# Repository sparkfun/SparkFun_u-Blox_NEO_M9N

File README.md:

SparkFun GPS NEO-M9N Breakout (Chip Antenna, U.FL, SMA) 
========================================

<table class="table table-hover table-striped table-bordered">
  <tr align="center">
   <td></td>
   <td></td>
    <td></td>
  </tr>
  <tr align="center">
    <td><a href="https://www.sparkfun.com/products/15733">SparkFun GPS NEO-M9N Chip Antenna <br />(GPS-15733)</a></td>
    <td><a href="https://www.sparkfun.com/products/15712">SparkFun GPS NEO-M9N U.FL <br />(GPS-15172)</a></td>
    <td><a href="https://www.sparkfun.com/products/17285">SparkFun GPS NEO-M9N SMA <br />(GPS-17285)</a></td>
  </tr>
</table>

The SparkFun NEO-M9N GPS Breakout is a high quality, GPS board with equally impressive configuration options. The NEO-M9N module is a 92-channel u-blox M9 engine GNSS receiver, meaning it can receive signals from the GPS, GLONASS, Galileo, and BeiDou constellations with ~1.5 meter accuracy. This breakout supports concurrent reception of four GNSS maximizes position accuracy in challenging conditions increasing precision and decreases lock time and thanks to the onboard rechargeable battery, you'll have backup power enabling the GPS to get a hot lock within seconds! Additionally, this u-blox receiver supports I<sup>2</sup>C (u-blox calls this Display Data Channel) which made it perfect for the Qwiic compatibility so we don't have to use up our precious UART ports. Utilizing our handy Qwiic system, no soldering is required to connect it to the rest of your system. However, we still have broken out 0.1"-spaced pins in case you prefer to use a breadboard. 

The NEO-M9N module detects jamming and spoofing events and can reports them to the host, so that the system can react to such events. A SAW (Surface Acoustic Wave) filter combined with an LNA (Low Noise Amplifier) in the RF path is integrated into the NEO-M9N module which allows normal operation even under strong RF interferences.

U-blox based GPS products are configurable using the popular, but dense, windows program called u-center. Plenty of different functions can be configured on the NEO-M9N: baud rates, update rates, geofencing, spoofing detection, external interrupts, SBAS/D-GPS, etc. All of this can be done within the SparkFun Arduino Library!

The SparkFun NEO-M9N GPS Breakout is also equipped with an on-board rechargeable battery that provides power to the RTC on the NEO-M9N.  This reduces the time-to-first fix from a cold start (~24s) to a hot start (~2s). The battery will maintain RTC and GNSS orbit data without being connected to power for plenty of time. 

Repository Contents
-------------------

* **/Documentation** - Data sheets for the NEO-M9N
* **/Hardware** - Eagle design files (.brd, .sch)
* **/Production** - Production panel files (.brd)

Documentation
--------------
* **[Library](https://github.com/sparkfun/SparkFun_u-blox_GNSS_Arduino_Library)** - Arduino Library the SparkFun GPS NEO-M9N.
* **[Qwiic UBlox GPS Py](https://github.com/sparkfun/Qwiic_Ublox_Gps_Py)** - Python Package
* **[Hookup Guide](https://learn.sparkfun.com/tutorials/sparkfun-gps-neo-m9n-hookup-guide)** - Basic hookup guide for the SparkFun GPS NEO-M9N

Product Versions
----------------
* [GPS-17285](https://www.sparkfun.com/products/17285) - GPS NEO-M9N SMA
* [GPS-15733](https://www.sparkfun.com/products/15733) - GPS NEO-M9N Chip Antenna
* [GPS-15712](https://www.sparkfun.com/products/15712) - GPS NEO-M9N u.FL

License Information
-------------------

This product is _**open source**_! 

Please review the LICENSE.md file for license information. 

If you have any questions or concerns on licensing, please contact technical support on our [SparkFun forums](https://forum.sparkfun.com/viewforum.php?f=152).

Distributed as-is; no warranty is given.

- Your friends at SparkFun.

_<COLLABORATION CREDIT>_

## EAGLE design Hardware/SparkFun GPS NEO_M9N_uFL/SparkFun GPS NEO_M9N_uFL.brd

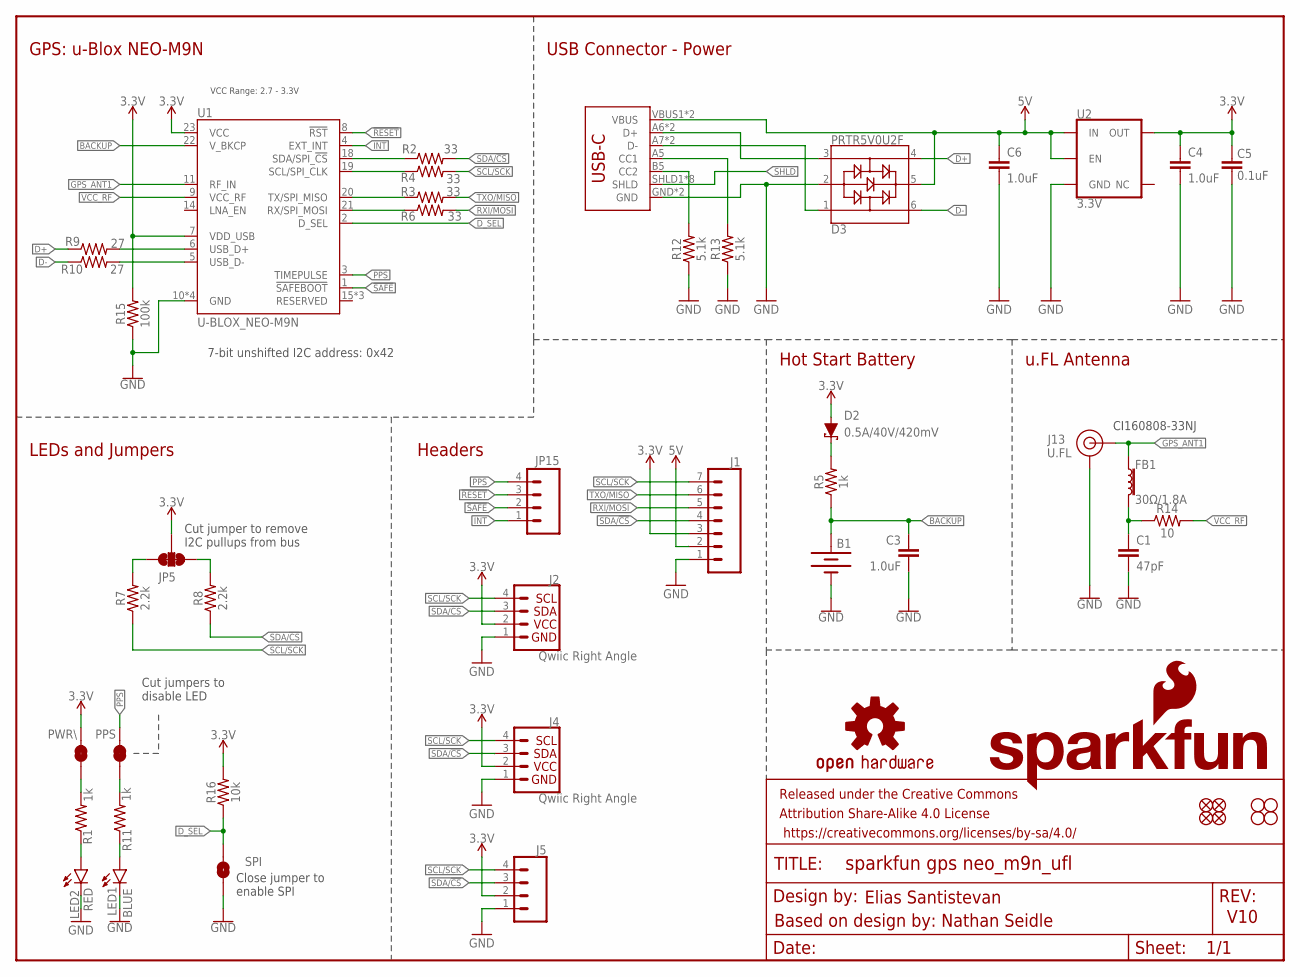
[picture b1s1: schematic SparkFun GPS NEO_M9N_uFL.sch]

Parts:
B1: 6.8MM_COIN_CELL; ML414H_IV01E
C1: 47pF; 0603
C3, C4, C6: 1.0uF; 0603
C5: 0.1uF; 0603
D2: 0.5A/40V/420mV; SOD-323
D3: PRTR5V0U2F; SOT886
FB1: 30Ω/1.8A; 0603
FRAME1: FRAME-LETTER; CREATIVE_COMMONS
J1: CONN_07NO_SILK; 1X07_NO_SILK
J2, J4: Qwiic Right Angle; JST04_1MM_RA
J3: USB_C2-LAYER; USB-C-16P
J5: CONN_041X04_NO_SILK; 1X04_NO_SILK
J13: U.FL
JP5: JUMPER-SMT_3_2-NC_TRACE_SILK; SMT-JUMPER_3_2-NC_TRACE_SILK
JP15: CONN_041X04_NO_SILK; 1X04_NO_SILK
JP21, JP61, JP71, JP81: FIDUCIALUFIDUCIAL; MICRO-FIDUCIAL
JP31, JP41, JP91, JP101: STAND-OFF
LED1: BLUE; LED-0603
LED2: RED; LED-0603
LOGO1: OSHW-LOGOMINI; OSHW-LOGO-MINI
LOGO2: SFE_LOGO_NAME_FLAME.1_INCH; SFE_LOGO_NAME_FLAME_.1
PPS: JUMPER-SMT_2_NC_TRACE_SILK; SMT-JUMPER_2_NC_TRACE_SILK
PWR\: JUMPER-SMT_2_NC_TRACE_SILK; SMT-JUMPER_2_NC_TRACE_SILK
R1, R5, R11: 1k; 0603
R2, R3, R4, R6: 33; 0603
R7, R8: 2.2k; 0603
R9, R10: 27; 0603
R12, R13: 5.1k; 0603
R14: 10; 0603
R15: 100k; 0603
R16: 10k; 0402
SPI: JUMPER-SMT_2_NO_SILK; SMT-JUMPER_2_NO_SILK
U1: U-BLOX_NEO-M9N; NEO-M9N
U2: 3.3V; SOT23-5

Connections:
3.3V: C4.1, C5.2, D2.A, J1.3, J2.2, J4.2, J5.2, JP5.2, PWR\.2, R15.2, R16.2, U1.7 (VDD_USB), U1.23 (VCC), U2.5 (OUT)
5V: C6.1, D3.5, J1.2, J3.VBUS1 (VBUS), J3.VBUS2 (VBUS), U2.1 (IN), U2.3 (EN)
!RESET: JP15.3, U1.8 (!RST)
!SAFE: JP15.2, U1.1 (!SAFEBOOT!)
ANT_VCC: C1.1, FB1.2, R14.1
BACKUP: B1.+, C3.1, R5.1, U1.22 (V_BKCP)
D+: D3.4, R9.1
D-: D3.6, R10.1
D_SEL: R16.1, SPI.2, U1.2 (D_SEL)
GND: B1.-, C1.2, C3.2, C4.2, C5.1, C6.2, D3.2, J1.1, J2.1, J3.GND, J3.GND2 (GND), J4.1, J5.1, J13.1 (GND), J13.2 (GND), LED1.C, LED2.C, R12.1, R13.1, R15.1, SPI.1, U1.10 (GND), U1.12 (GND), U1.13 (GND), U1.24 (GND), U2.2 (GND)
GPS_ANT1: FB1.1, J13.FEED (SIGNAL), U1.11 (RF_IN)
INT: JP15.1, U1.4 (EXT_INT)
unnamed: PWR\.1, R1.2
unnamed: LED1.A, R11.1
unnamed: PPS.1, R11.2
unnamed: JP5.1, R8.2
unnamed: D2.C, R5.2
unnamed: J3.B5 (CC2), R12.2
unnamed: JP5.3, R7.2
unnamed: J3.A5 (CC1), R13.2
unnamed: LED2.A, R1.1
unnamed: R9.2, U1.6 (USB_D+)
unnamed: R10.2, U1.5 (USB_D-)
PPS: JP15.4, PPS.2, U1.3 (TIMEPULSE)
RXI/MOSI: J1.5, R6.2
RXLV: R6.1, U1.21 (RX/SPI_MOSI)
SCL/SCK: J1.7, J2.4, J4.4, J5.4, R4.2, R7.1
SCL_LV: R4.1, U1.19 (SCL/SPI_CLK)
SDA/!CS: J1.4, J2.3, J4.3, J5.3, R2.2, R8.1
SDA_LV: R2.1, U1.18 (SDA/SPI_!CS!)
SHLD: J3.SHLD1 (SHLD), J3.SHLD2 (SHLD), J3.SHLD3 (SHLD), J3.SHLD4 (SHLD), J3.SHLD5 (SHLD), J3.SHLD6 (SHLD), J3.SHLD7 (SHLD), J3.SHLD8 (SHLD)
TXLV: R3.1, U1.20 (TX/SPI_MISO)
TXO/MISO: J1.6, R3.2
USB_D+: D3.3, J3.A6 (D+), J3.B6 (D+)
USB_D-: D3.1, J3.A7 (D-), J3.B7 (D-)
VCC_RF: R14.2, U1.9 (VCC_RF)

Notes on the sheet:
V10
7-bit unshifted I2C address: 0x42
Cut jumper to remove I2C pullups from bus
Cut jumpers to disable LED
Close jumper to enable SPI
CI160808-33NJ
Elias Santistevan
Headers
LEDs and Jumpers
Hot Start Battery
GPS: u-Blox NEO-M9N
u.FL Antenna
USB Connector - Power
Based on design by: Nathan Seidle
VCC Range: 2.7 - 3.3V

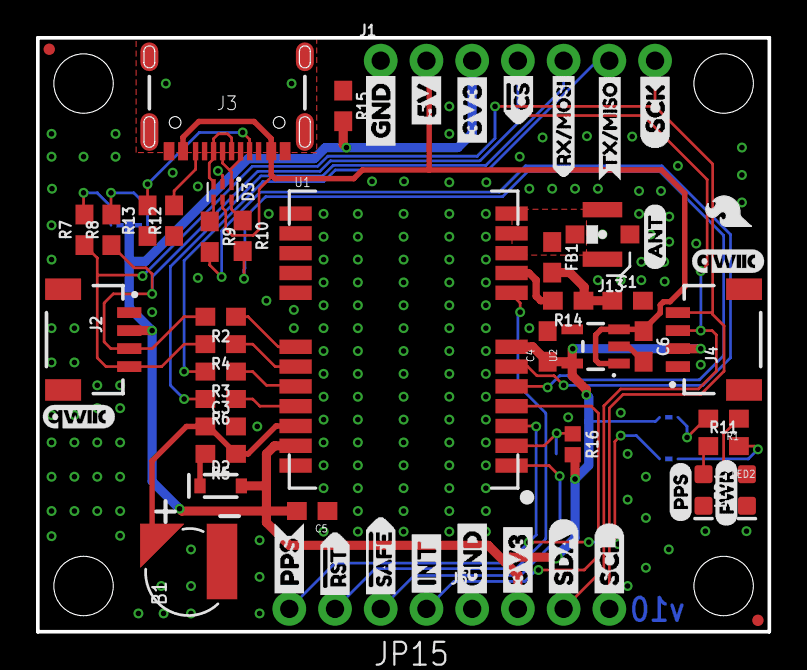
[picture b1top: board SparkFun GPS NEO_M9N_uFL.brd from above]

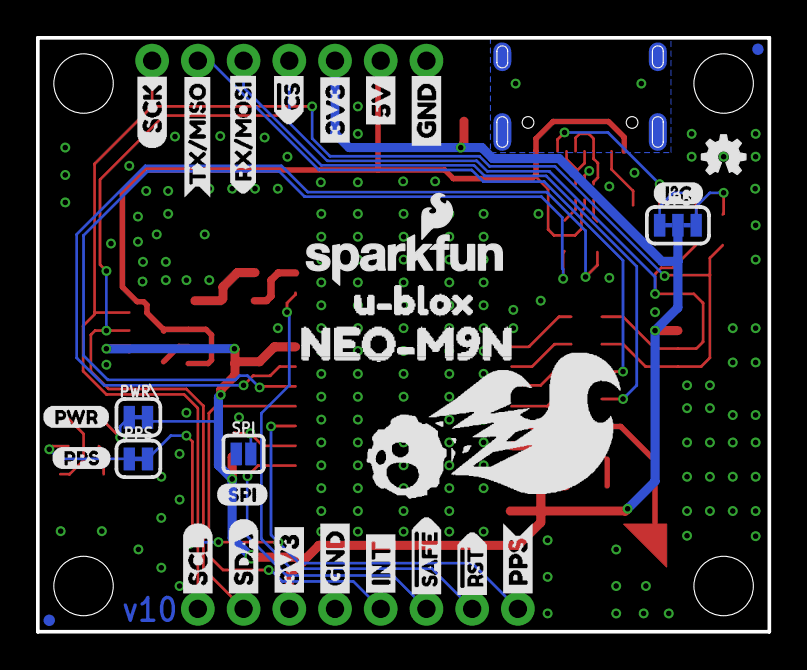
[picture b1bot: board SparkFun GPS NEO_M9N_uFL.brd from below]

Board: 2 copper layers, 40.6 x 33.0 mm, 94 parts (30 on the bottom side), 36 nets.

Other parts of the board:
U$1, U$4: SDA-[)
U$2: NEO#M9N1
U$3, U$5: SCL-[)
U$6, U$7, U$60, U$61: 3V3-04
U$8, U$9, U$62, U$63: GND-04
U$10: I_SUPER2_C-()-03
U$11: SPI1
U$12, U$52: PPS0
U$13, U$14: QWIIC_4MM
U$15, U$16: INT8
U$17: PWR1
U$18: PWR-()-03
U$19, U$20: 5V
U$21: NEO_GPS_BOARD_SILK_FINAL#03#JPG
U$22: U#BLOX3
U$23, U$24: CS#-<]
U$25: ANT0
U$26: RX#MOSI2
U$31: RX#MOSI3
U$33: SFE_LOGO_FLAME_.1
U$34: TX#MISO0
U$35, U$36: #RST3
U$37: TX#MISO1
U$38, U$41: SCK-(]-04
U$39, U$40: #SAFE1
U$43, U$44: PPS5

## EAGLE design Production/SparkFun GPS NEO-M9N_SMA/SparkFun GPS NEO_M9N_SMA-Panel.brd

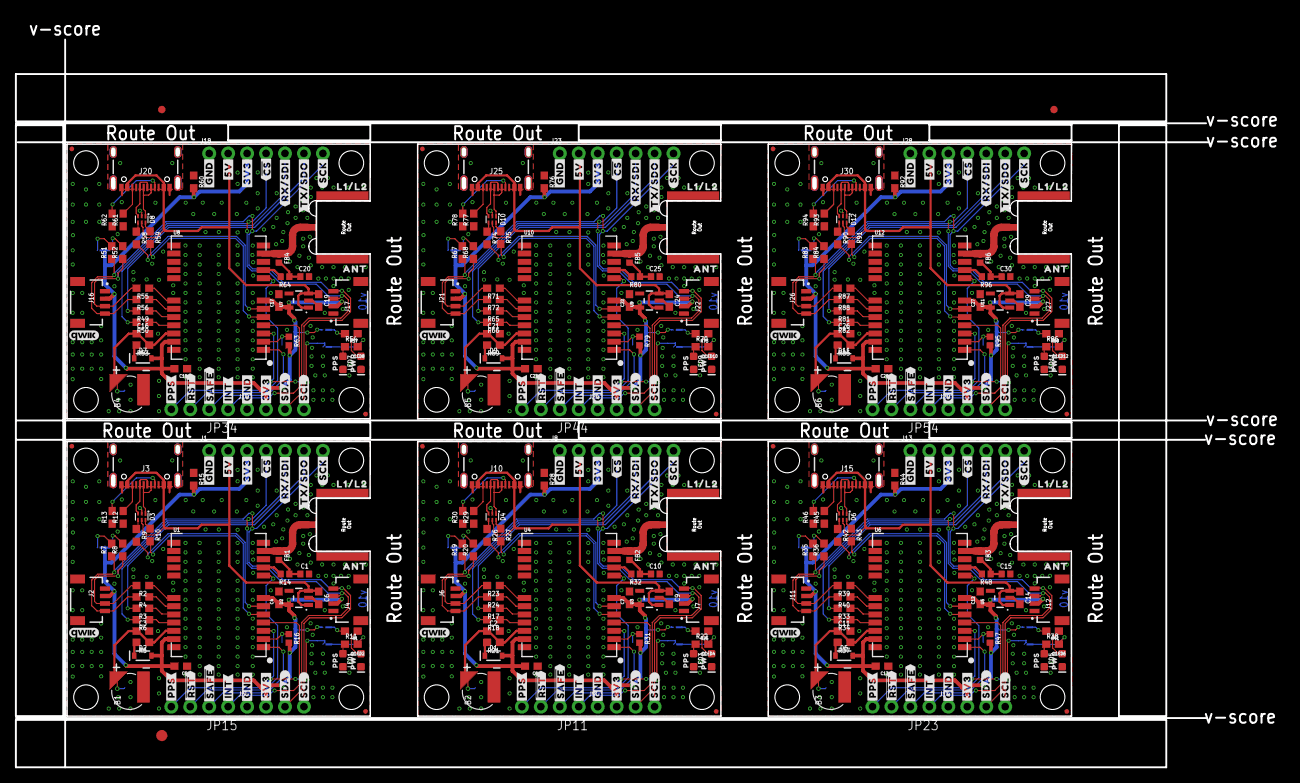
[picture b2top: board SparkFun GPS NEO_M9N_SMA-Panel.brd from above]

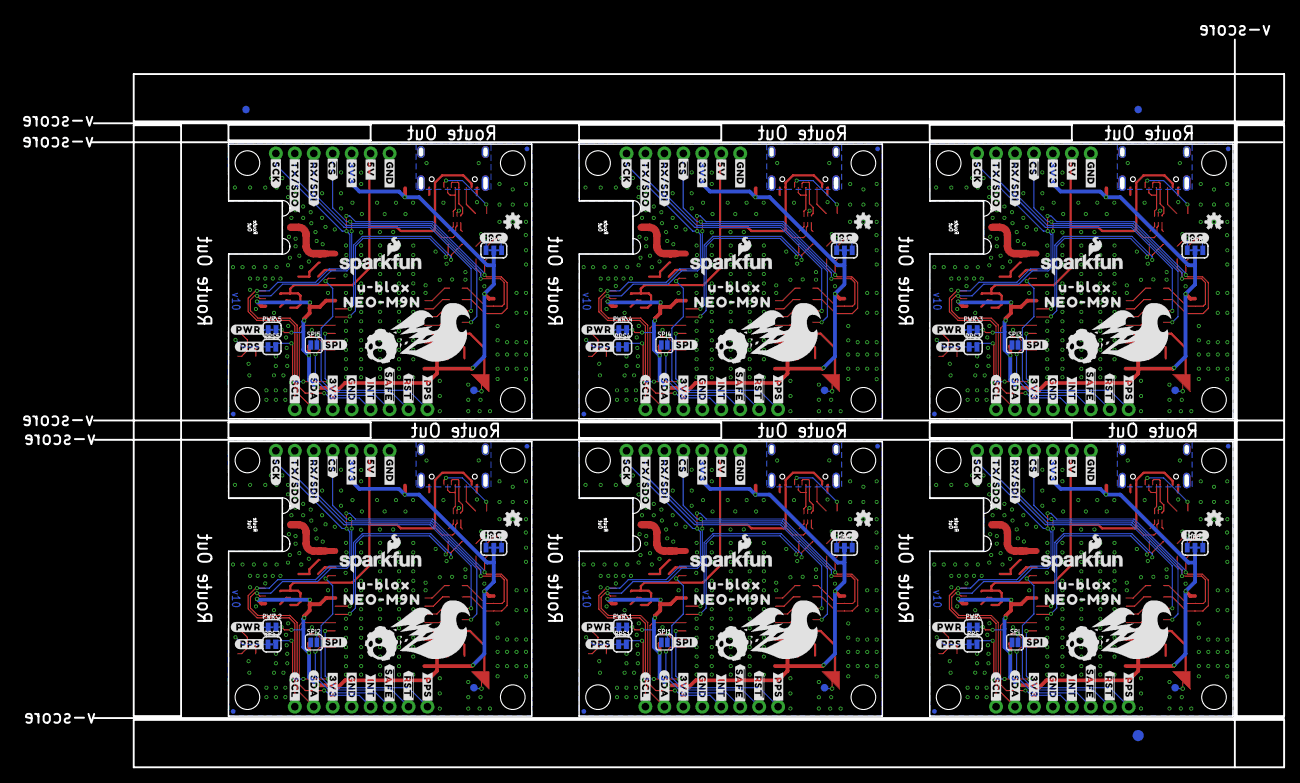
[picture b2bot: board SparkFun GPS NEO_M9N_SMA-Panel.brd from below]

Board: 2 copper layers, 159.8 x 97.5 mm, 564 parts (189 on the bottom side), 216 nets.

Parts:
B1, B2, B3, B4, B5, B6: 6.8MM_COIN_CELL; ML414H_IV01E
C1, C10, C15, C20, C25, C30: 47pF; 0402
C2, C3, C4, C6, C7, C9, C11, C12, C14, C16, C17, C19, C21, C22, C24, C26, C27, C29: 1.0uF; 0603
C5, C8, C13, C18, C23, C28: 0.1uF; 0603
D1, D2, D5, D7, D9, D11: 0.5A/40V/420mV; SOD-323
D3, D4, D6, D8, D10, D12: PRTR5V0U2F; SOT886
E1, E2, E3, E4, E5, E6: ANTENNA-GROUNDEDEDGE_SMA_SMD; SMA-EDGE-SMD
E$1, E$2, E$3, E$4: FIDUCIAL-1X2
E$5, E$6: FIDUCIAL-1.5X3
FB1, FB2, FB3, FB4, FB5, FB6: FERRITE_BEAD-120_OHM-0402; 0402
J1, J8, J13, J18, J23, J28: 1X07_NO_SILK
J2, J4, J6, J7, J11, J12, J16, J17, J21, J22, J26, J27: Qwiic Right Angle; JST04_1MM_RA
J3, J10, J15, J20, J25, J30: USB-C-16P-2LAYER-PADS
J5, J9, J14, J19, J24, J29: 1X04_NO_SILK
JP1, JP2, JP9, JP10, JP12, JP13, JP20, JP22, JP24, JP25, JP31, JP32, JP33, JP35, JP36, JP42, JP43, JP45, JP46, JP52, JP53, JP55, JP91, JP101: STAND-OFF
JP3, JP4, JP7, JP8, JP14, JP16, JP18, JP19, JP21, JP26, JP27, JP29, JP30, JP37, JP38, JP40, JP41, JP47, JP48, JP50, JP51, JP61, JP71, JP81: FIDUCIALUFIDUCIAL; MICRO-FIDUCIAL
JP5, JP6, JP17, JP28, JP39, JP49: JUMPER-SMT_3_2-NC_TRACE_SILK; SMT-JUMPER_3_2-NC_TRACE_SILK
JP11, JP15, JP23, JP34, JP44, JP54: 1X04_NO_SILK
LED1, LED3, LED5, LED7, LED9, LED11: BLUE; LED-0603
LED2, LED4, LED6, LED8, LED10, LED12: RED; LED-0603
LOGO1, LOGO3, LOGO5, LOGO7, LOGO9, LOGO11: OSHW-LOGOMINI; OSHW-LOGO-MINI
LOGO2, LOGO4, LOGO6, LOGO8, LOGO10, LOGO12: SFE_LOGO_NAME_FLAME.1_INCH; SFE_LOGO_NAME_FLAME_.1
PPS, PPS1, PPS2, PPS3, PPS4, PPS5: JUMPER-SMT_2_NC_TRACE_SILK; SMT-JUMPER_2_NC_TRACE_SILK
PWR\, PWR\1, PWR\2, PWR\3, PWR\4, PWR\5: JUMPER-SMT_2_NC_TRACE_SILK; SMT-JUMPER_2_NC_TRACE_SILK
R1, R5, R11, R21, R22, R25, R37, R38, R41, R53, R54, R57, R69, R70, R73, R85, R86, R89: 1k; 0603
R2, R3, R4, R6, R17, R18, R23, R24, R33, R34, R39, R40, R49, R50, R55, R56, R65, R66, R71, R72, R81, R82, R87, R88: 33; 0603
R7, R8, R19, R20, R35, R36, R51, R52, R67, R68, R83, R84: 2.2k; 0603
R9, R10, R26, R27, R42, R43, R58, R59, R74, R75, R90, R91: 27; 0603
R12, R13, R29, R30, R45, R46, R61, R62, R77, R78, R93, R94: 5.1k; 0603
R14, R32, R48, R64, R80, R96: 33; 0402
R15, R28, R44, R60, R76, R92: 100k; 0603
R16, R31, R47, R63, R79, R95: 10k; 0402
SPI, SPI1, SPI2, SPI3, SPI4, SPI5: JUMPER-SMT_2_NO_SILK; SMT-JUMPER_2_NO_SILK
TP1, TP2, TP3, TP4, TP5, TP6: TEST-POINT3X4; PAD.03X.04
U1, U4, U6, U8, U10, U12: U-BLOX_NEO-M9N; NEO-M9N/M8T/M8U
U2, U3, U5, U7, U9, U11: 3.3V; SOT23-5
U$1, U$45, U$87, U$129, U$171, U$213: ##CS##9
U$2, U$62, U$104, U$146, U$188, U$230: U#BLOX19
U$3, U$46, U$88, U$130, U$172, U$214: ##SAFE##15
U$4, U$5, U$39, U$40, U$47, U$48, U$78, U$79, U$89, U$90, U$120, U$121, U$131, U$132, U$162, U$163, U$173, U$174, U$204, U$205, U$215, U$216, U$246, U$247: #3V3#6
U$6, U$42, U$49, U$81, U$91, U$123, U$133, U$165, U$175, U$207, U$217, U$249: #5V#1
U$7, U$8, U$38, U$41, U$50, U$51, U$77, U$80, U$92, U$93, U$119, U$122, U$134, U$135, U$161, U$164, U$176, U$177, U$203, U$206, U$218, U$219, U$245, U$248: #GND#0
U$9, U$52, U$94, U$136, U$178, U$220: #INT#16
U$10, U$83, U$125, U$167, U$209, U$251: PPS7
U$11, U$32, U$53, U$71, U$95, U$113, U$137, U$155, U$179, U$197, U$221, U$239: #PPS#13
U$12, U$63, U$105, U$147, U$189, U$231: #SPI#22
U$13, U$84, U$126, U$168, U$210, U$252: PWR6
U$14, U$43, U$85, U$127, U$169, U$211: QWIIC_4MM
U$15, U$54, U$96, U$138, U$180, U$222: #RX#SDI#10
U$16, U$55, U$97, U$139, U$181, U$223: #SCK#12
U$17, U$72, U$114, U$156, U$198, U$240: #PWR#1
U$18, U$56, U$98, U$140, U$182, U$224: #SCL#18
U$19, U$57, U$99, U$141, U$183, U$225: #SDA#17
U$20, U$58, U$100, U$142, U$184, U$226: #TX#SDO#11
U$21, U$44, U$86, U$128, U$170, U$212: NEO_GPS_BOARD_SILK_FINAL#03#JPG
U$22, U$67, U$109, U$151, U$193, U$235: ##SAFE##11
U$23, U$59, U$101, U$143, U$185, U$227: L1#L28
U$24, U$60, U$102, U$144, U$186, U$228: ANT8
U$25, U$61, U$103, U$145, U$187, U$229: NEO#M9N20
U$26, U$64, U$106, U$148, U$190, U$232: ##CS##6
U$27, U$65, U$107, U$149, U$191, U$233: ##RST##12
U$28, U$66, U$108, U$150, U$192, U$234: ##RST##2
U$29, U$68, U$110, U$152, U$194, U$236: #I2C#3
U$30, U$69, U$111, U$153, U$195, U$237: #INT#10
U$31, U$70, U$112, U$154, U$196, U$238: #PPS#0
U$33, U$73, U$115, U$157, U$199, U$241: #RX#SDI#4
U$34, U$74, U$116, U$158, U$200, U$242: #SCK#3
U$35, U$75, U$117, U$159, U$201, U$243: #SCL#8
U$36, U$76, U$118, U$160, U$202, U$244: #SDA#9
U$37, U$82, U$124, U$166, U$208, U$250: #TX#SDO#5

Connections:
3.3V: C4.1, C5.2, D2.A, J1.3, J2.2, J4.2, J5.2, JP5.2, PWR\.2, R15.2, R16.2, U1.7, U1.23, U2.5
3.3V1: C7.1, C8.2, D1.A, J6.2, J7.2, J8.3, J9.2, JP6.2, PWR\1.2, R28.2, R31.2, U3.5, U4.7, U4.23
3.3V2: C12.1, C13.2, D5.A, J11.2, J12.2, J13.3, J14.2, JP17.2, PWR\2.2, R44.2, R47.2, U5.5, U6.7, U6.23
3.3V3: C17.1, C18.2, D7.A, J16.2, J17.2, J18.3, J19.2, JP28.2, PWR\3.2, R60.2, R63.2, U7.5, U8.7, U8.23
3.3V4: C22.1, C23.2, D9.A, J21.2, J22.2, J23.3, J24.2, JP39.2, PWR\4.2, R76.2, R79.2, U9.5, U10.7, U10.23
3.3V5: C27.1, C28.2, D11.A, J26.2, J27.2, J28.3, J29.2, JP49.2, PWR\5.2, R92.2, R95.2, U11.5, U12.7, U12.23
5V: C6.1, D3.5, J1.2, J3.VBUS1, J3.VBUS2, U2.1, U2.3
5V1: C9.1, D4.5, J8.2, J10.VBUS1, J10.VBUS2, U3.1, U3.3
5V2: C14.1, D6.5, J13.2, J15.VBUS1, J15.VBUS2, U5.1, U5.3
5V3: C19.1, D8.5, J18.2, J20.VBUS1, J20.VBUS2, U7.1, U7.3
5V4: C24.1, D10.5, J23.2, J25.VBUS1, J25.VBUS2, U9.1, U9.3
5V5: C29.1, D12.5, J28.2, J30.VBUS1, J30.VBUS2, U11.1, U11.3
!RESET: JP15.3, U1.8
!RESET1: JP11.3, U4.8
!RESET2: JP23.3, U6.8
!RESET3: JP34.3, U8.8
!RESET4: JP44.3, U10.8
!RESET5: JP54.3, U12.8
!SAFE: JP15.2, U1.1
!SAFE1: JP11.2, U4.1
!SAFE2: JP23.2, U6.1
!SAFE3: JP34.2, U8.1
!SAFE4: JP44.2, U10.1
!SAFE5: JP54.2, U12.1
D+: D3.4, R9.1
D+1: D4.4, R26.1
D+2: D6.4, R42.1
D+3: D8.4, R58.1
D+4: D10.4, R74.1
D+5: D12.4, R90.1
D-: D3.6, R10.1
D-1: D4.6, R27.1
D-2: D6.6, R43.1
D-3: D8.6, R59.1
D-4: D10.6, R75.1
D-5: D12.6, R91.1
D_SEL: R16.1, SPI.2, U1.2
D_SEL1: R31.1, SPI1.2, U4.2
D_SEL2: R47.1, SPI2.2, U6.2
D_SEL3: R63.1, SPI3.2, U8.2
D_SEL4: R79.1, SPI4.2, U10.2
D_SEL5: R95.1, SPI5.2, U12.2
GND: B1.-, C1.2, C3.2, C4.2, C5.1, C6.2, D3.2, E1.GND@0, E1.GND@1, J1.1, J2.1, J3.GND, J3.GND2, J4.1, J5.1, LED1.C, LED2.C, R12.1, R13.1, R15.1, SPI.1, U1.10, U1.12, U1.13, U1.24, U2.2
GND1: B2.-, C2.2, C7.2, C8.1, C9.2, C10.2, D4.2, E2.GND@0, E2.GND@1, J6.1, J7.1, J8.1, J9.1, J10.GND, J10.GND2, LED3.C, LED4.C, R28.1, R29.1, R30.1, SPI1.1, U3.2, U4.10, U4.12, U4.13, U4.24
GND2: B3.-, C11.2, C12.2, C13.1, C14.2, C15.2, D6.2, E3.GND@0, E3.GND@1, J11.1, J12.1, J13.1, J14.1, J15.GND, J15.GND2, LED5.C, LED6.C, R44.1, R45.1, R46.1, SPI2.1, U5.2, U6.10, U6.12, U6.13, U6.24
GND3: B4.-, C16.2, C17.2, C18.1, C19.2, C20.2, D8.2, E4.GND@0, E4.GND@1, J16.1, J17.1, J18.1, J19.1, J20.GND, J20.GND2, LED7.C, LED8.C, R60.1, R61.1, R62.1, SPI3.1, U7.2, U8.10, U8.12, U8.13, U8.24
GND4: B5.-, C21.2, C22.2, C23.1, C24.2, C25.2, D10.2, E5.GND@0, E5.GND@1, J21.1, J22.1, J23.1, J24.1, J25.GND, J25.GND2, LED9.C, LED10.C, R76.1, R77.1, R78.1, SPI4.1, U9.2, U10.10, U10.12, U10.13, U10.24
GND5: B6.-, C26.2, C27.2, C28.1, C29.2, C30.2, D12.2, E6.GND@0, E6.GND@1, J26.1, J27.1, J28.1, J29.1, J30.GND, J30.GND2, LED11.C, LED12.C, R92.1, R93.1, R94.1, SPI5.1, U11.2, U12.10, U12.12, U12.13, U12.24
GPS_ANT1: E1.SIG, FB1.1, U1.11
GPS_ANT2: E2.SIG, FB2.1, U4.11
GPS_ANT3: E3.SIG, FB3.1, U6.11
GPS_ANT4: E4.SIG, FB4.1, U8.11
GPS_ANT5: E5.SIG, FB5.1, U10.11
GPS_ANT6: E6.SIG, FB6.1, U12.11
INT: JP15.1, U1.4
INT1: JP11.1, U4.4
INT2: JP23.1, U6.4
INT3: JP34.1, U8.4
INT4: JP44.1, U10.4
INT5: JP54.1, U12.4
unnamed: PWR\.1, R1.2
unnamed: LED1.A, R11.1
unnamed: C1.1, FB1.2, R14.1
unnamed: PPS.1, R11.2
unnamed: JP5.1, R8.2
unnamed: D2.C, R5.2
unnamed: J3.B5, R12.2
unnamed: JP5.3, R7.2
unnamed: J3.A5, R13.2
unnamed: LED2.A, R1.1
unnamed: R9.2, U1.6
unnamed: R10.2, U1.5
unnamed: JP6.1, R20.2
unnamed: JP6.3, R19.2
unnamed: LED3.A, R22.1
unnamed: PPS1.1, R22.2
unnamed: D1.C, R21.2
unnamed: LED4.A, R25.1
unnamed: R26.2, U4.6
unnamed: R27.2, U4.5
unnamed: PWR\1.1, R25.2
unnamed: J10.B5, R29.2
unnamed: J10.A5, R30.2
unnamed: C10.1, FB2.2, R32.1
unnamed: JP17.1, R36.2
unnamed: JP17.3, R35.2
unnamed: LED5.A, R38.1
unnamed: PPS2.1, R38.2
unnamed: D5.C, R37.2
unnamed: LED6.A, R41.1
unnamed: R42.2, U6.6
unnamed: R43.2, U6.5
unnamed: PWR\2.1, R41.2
unnamed: J15.B5, R45.2
unnamed: J15.A5, R46.2
unnamed: C15.1, FB3.2, R48.1
unnamed: JP28.1, R52.2
unnamed: JP28.3, R51.2
unnamed: LED7.A, R54.1
unnamed: PPS3.1, R54.2
unnamed: D7.C, R53.2
unnamed: LED8.A, R57.1
unnamed: R58.2, U8.6
unnamed: R59.2, U8.5
unnamed: PWR\3.1, R57.2
unnamed: J20.B5, R61.2
unnamed: J20.A5, R62.2
unnamed: C20.1, FB4.2, R64.1
unnamed: JP39.1, R68.2
unnamed: JP39.3, R67.2
unnamed: LED9.A, R70.1
unnamed: PPS4.1, R70.2
unnamed: D9.C, R69.2
unnamed: LED10.A, R73.1
unnamed: R74.2, U10.6
unnamed: R75.2, U10.5
unnamed: PWR\4.1, R73.2
unnamed: J25.B5, R77.2
unnamed: J25.A5, R78.2
unnamed: C25.1, FB5.2, R80.1
unnamed: JP49.1, R84.2
unnamed: JP49.3, R83.2
unnamed: LED11.A, R86.1
unnamed: PPS5.1, R86.2
unnamed: D11.C, R85.2
unnamed: LED12.A, R89.1
unnamed: R90.2, U12.6
unnamed: R91.2, U12.5
unnamed: PWR\5.1, R89.2
unnamed: J30.B5, R93.2
unnamed: J30.A5, R94.2
unnamed: C30.1, FB6.2, R96.1
PPS: JP15.4, PPS.2, U1.3
PPS1: JP11.4, PPS1.2, U4.3
PPS2: JP23.4, PPS2.2, U6.3
PPS3: JP34.4, PPS3.2, U8.3
PPS4: JP44.4, PPS4.2, U10.3
PPS5: JP54.4, PPS5.2, U12.3
RXI/SDI: J1.5, R6.2
RXI/SDI1: J8.5, R18.2
RXI/SDI2: J13.5, R34.2
RXI/SDI3: J18.5, R50.2
RXI/SDI4: J23.5, R66.2
RXI/SDI5: J28.5, R82.2
RXLV: R6.1, U1.21
RXLV1: R18.1, U4.21
RXLV2: R34.1, U6.21
RXLV3: R50.1, U8.21
RXLV4: R66.1, U10.21
RXLV5: R82.1, U12.21
SCL/SCK: J1.7, J2.4, J4.4, J5.4, R4.2, R7.1
SCL/SCK1: J6.4, J7.4, J8.7, J9.4, R19.1, R24.2
SCL/SCK2: J11.4, J12.4, J13.7, J14.4, R35.1, R40.2
SCL/SCK3: J16.4, J17.4, J18.7, J19.4, R51.1, R56.2
SCL/SCK4: J21.4, J22.4, J23.7, J24.4, R67.1, R72.2
SCL/SCK5: J26.4, J27.4, J28.7, J29.4, R83.1, R88.2
SCL_LV: R4.1, U1.19
SCL_LV1: R24.1, U4.19
SCL_LV2: R40.1, U6.19
SCL_LV3: R56.1, U8.19
SCL_LV4: R72.1, U10.19
SCL_LV5: R88.1, U12.19
SDA/!CS: J1.4, J2.3, J4.3, J5.3, R2.2, R8.1
SDA/!CS1: J6.3, J7.3, J8.4, J9.3, R20.1, R23.2
SDA/!CS2: J11.3, J12.3, J13.4, J14.3, R36.1, R39.2
SDA/!CS3: J16.3, J17.3, J18.4, J19.3, R52.1, R55.2
SDA/!CS4: J21.3, J22.3, J23.4, J24.3, R68.1, R71.2
SDA/!CS5: J26.3, J27.3, J28.4, J29.3, R84.1, R87.2
SDA_LV: R2.1, U1.18
SDA_LV1: R23.1, U4.18
SDA_LV2: R39.1, U6.18
SDA_LV3: R55.1, U8.18
SDA_LV4: R71.1, U10.18
SDA_LV5: R87.1, U12.18
SHLD: J3.SHLD1, J3.SHLD2, J3.SHLD3, J3.SHLD4
SHLD1: J10.SHLD1, J10.SHLD2, J10.SHLD3, J10.SHLD4
SHLD2: J15.SHLD1, J15.SHLD2, J15.SHLD3, J15.SHLD4
SHLD3: J20.SHLD1, J20.SHLD2, J20.SHLD3, J20.SHLD4
SHLD4: J25.SHLD1, J25.SHLD2, J25.SHLD3, J25.SHLD4
SHLD5: J30.SHLD1, J30.SHLD2, J30.SHLD3, J30.SHLD4
TXLV: R3.1, U1.20
TXLV1: R17.1, U4.20
TXLV2: R33.1, U6.20
TXLV3: R49.1, U8.20
TXLV4: R65.1, U10.20
TXLV5: R81.1, U12.20
TXO/SDO: J1.6, R3.2
TXO/SDO1: J8.6, R17.2
TXO/SDO2: J13.6, R33.2
TXO/SDO3: J18.6, R49.2
TXO/SDO4: J23.6, R65.2
TXO/SDO5: J28.6, R81.2
USB_D+: D3.3, J3.A6, J3.B6
USB_D+1: D4.3, J10.A6, J10.B6
USB_D+2: D6.3, J15.A6, J15.B6
USB_D+3: D8.3, J20.A6, J20.B6
USB_D+4: D10.3, J25.A6, J25.B6
USB_D+5: D12.3, J30.A6, J30.B6
USB_D-: D3.1, J3.A7, J3.B7
USB_D-1: D4.1, J10.A7, J10.B7
USB_D-2: D6.1, J15.A7, J15.B7
USB_D-3: D8.1, J20.A7, J20.B7
USB_D-4: D10.1, J25.A7, J25.B7
USB_D-5: D12.1, J30.A7, J30.B7
VCC_RF: R14.2, U1.9
VCC_RF1: R32.2, U4.9
VCC_RF2: R48.2, U6.9
VCC_RF3: R64.2, U8.9
VCC_RF4: R80.2, U10.9
VCC_RF5: R96.2, U12.9
V_BATT: B1.+, C3.1, R5.1, TP1.P$1, U1.22
V_BATT1: B2.+, C2.1, R21.1, TP2.P$1, U4.22
V_BATT2: B3.+, C11.1, R37.1, TP3.P$1, U6.22
V_BATT3: B4.+, C16.1, R53.1, TP4.P$1, U8.22
V_BATT4: B5.+, C21.1, R69.1, TP5.P$1, U10.22
V_BATT5: B6.+, C26.1, R85.1, TP6.P$1, U12.22

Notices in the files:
parts and their libraries:
SparkFun-Resistors: Licensing: Creative Commons ShareAlike 4.0 International - https://creativecommons.org/licenses/by-sa/4.0
SparkFun-Aesthetics: Released under the Creative Commons Attribution Share-Alike 4.0 License
SparkFun-Aesthetics: https://creativecommons.org/licenses/by-sa/4.0
